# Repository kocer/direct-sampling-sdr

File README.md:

# Direct-Sampling SDR

A direct-sampling software-defined radio transceiver and its power
amplifier for the amateur bands from 1.8 MHz to 54 MHz.

## What the equipment does

The receiver samples the antenna signal directly. It does not use a
mixer and it does not use an intermediate frequency. Four receive
channels operate at the same time. The four channels use one clock.
Thus the channels keep a constant phase relation.

The transmitter uses the same four channels in the opposite direction.
The power amplifier increases the transmit power to a maximum of 100 W.

| Item | Value |
|---|---|
| Frequency range | 1.8 MHz to 54 MHz |
| Receive channels | 4, phase coherent |
| Transmit channels | 4 |
| ADC | AD9251BCPZ-80, 14 bit, dual, 80 MSPS |
| DAC | AD9767, 14 bit, dual, operated at 80 MSPS |
| FPGA | Lattice ECP5 LFE5U-25F, BG256 |
| Filter bands | 7 for each channel |
| Amplifier power | 5, 10, 25, 50, 75 and 100 W |
| Amplifier class | A, at all power levels |
| Host interface | 2 x gigabit ethernet |
| Sample clock | 80.000 MHz VCXO, ABLNO-V |
| Clock jitter | 81 fs narrow band, 162 fs wide band |
| Reference | 10 MHz external, or GPS |

## The three boards

| Board | Function | Size | Layers |
|---|---|---|---|
| A | Main board: ADC, DAC, FPGA, ethernet | 235 x 225 mm | 6 |
| C | RF board: filters, transmit/receive relays | 350 x 235 mm | 2 |
| D | Power amplifier: driver, finals, low-pass filters | 275 x 185 mm | 2 |

Board B does not exist. The first design had a separate clock board.
The clock circuit is now on board A, because the distance from the clock
to the ADC controls the phase accuracy.

## Signal path

The receive path:

1. The antenna connects to board C.
2. The band filter removes the unwanted signals.
3. The transmit/receive relay connects the filter to the receive path.
4. The attenuator sets the signal level.
5. Board A receives the signal.
6. The transformer makes the signal differential.
7. The ADC samples the signal.
8. The FPGA processes the samples.
9. The ethernet interface sends the data to the host.

The transmit path:

1. The host sends the data to board A.
2. The DAC makes the analog signal.
3. Board D receives the signal.
4. The driver stage increases the power.
5. The four final transistors increase the power to 100 W.
6. The low-pass filter removes the harmonics.
7. The directional coupler measures the forward and the reflected power.
8. The antenna radiates the signal.

## Why direct sampling

A superheterodyne receiver mixes the input signal to a lower frequency.
The mixer makes unwanted products. The local oscillator adds noise.
Each conversion stage adds distortion.

A direct-sampling receiver has none of these stages. The ADC samples the
antenna signal. The remaining signal path is digital, thus it is exact
and it does not change with the temperature.

The clock sets the limit at high frequency. The jitter of the clock
gives this maximum signal-to-noise ratio:

    SNR = -20 x log10(2 x pi x f x t_jitter)

The VCXO contributes 60 fs and the fan-out buffer adds 54 fs in a narrow
band or 150 fs in a wide band. Together they give 81 fs and 162 fs.

| Input frequency | Jitter | SNR limit | What limits the result |
|---|---|---|---|
| 30 MHz | 81 fs | 96 dB | The noise of the ADC |
| 500 MHz | 81 fs | 72 dB | At the limit |
| 500 MHz | 162 fs | 66 dB | The jitter of the clock |

In the amateur bands the noise of the ADC is the limit and the clock is
not. The clock becomes the limit only when the receiver undersamples
near 500 MHz. A better clock part costs ten times more, and 66 dB is
still 11 effective bits.

## Why four coherent channels

Four channels that share one clock keep a constant phase relation. This
makes these functions possible:

- Removal of a local noise source with a second antenna
- Measurement of the direction of a signal
- Increase of the antenna gain in one direction
- Measurement of meteor trails with two or more sites

A receiver with one channel cannot do these functions.

## Licenses

| Content | License |
|---|---|
| Hardware design | CERN-OHL-S-2.0 |
| Software and scripts | GPL-3.0 |
| Documentation | CC-BY-SA-4.0 |

## Repository content

| Directory | Content |
|---|---|
| `hardware/kicad/A_main` | Board A: schematic, PCB, generator scripts |
| `hardware/kicad/C_rf` | Board C |
| `hardware/kicad/D_pa` | Board D |
| `hardware/kicad/lib` | Symbols and footprints |
| `gateware/rtl` | Verilog source for the ECP5 |
| `gateware/sim` | Test benches |
| `gateware/sentez` | Synthesis and place-and-route scripts |
| `docs` | Design documentation |

The schematics are not drawn by hand. Python scripts make them. Each
script writes one sheet. To change a sheet, change the script and run
it again. The document `docs/TOOLS.md` gives the procedure.

## Status

The three schematics are complete. The electrical rule check finds no
errors on the three boards. The placement is complete. The routing is
in progress. No board is ready for manufacture.

The gateware operates in simulation. 21 test benches pass. The design
fits in the ECP5-25F and it meets the timing of all five clocks. The
receive chain, the transmit chain, the packet interface and the
control interface are complete. The SDRAM interface and the digital
predistortion do not exist.

Verification tools examine the boards and the schematics. They find
faults that the electrical rule check cannot find. An example: a
symbol pin number that does not agree with a footprint pad number
makes a net that goes nowhere, but the rule check sees a correct
wire. The commit messages give the details of each fault.

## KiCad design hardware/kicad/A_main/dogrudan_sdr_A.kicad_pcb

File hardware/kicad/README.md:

# KiCad çalışma dizini

```
lib/dogrudan-sdr.kicad_sym   sembol kütüphanesi
lib/gen_symbols.py           üreteç — sembolleri BU yazıyor, elle düzenleme
lib/ATTRIBUTION.md           ECP5 sembolü kaynağı ve lisansı
A_main/                      A kartı (ADC+DAC+saat+FPGA+PHY+güç)
C_frontend/                  C kartı (koruma+T/R+zayıflatıcı+ön seçici)
```

## Semboller

| Sembol | Pin | Birim | Kaynak | Durum |
|---|---|---|---|---|
| ECP5-BGA256 | 256 | 8 | Cynthion (CERN-OHL-P) | pin uyumu doğrulandı |
| AD9251 | 65 | 4 | datasheet Rev.C s.11-12 | görsel doğrulandı |
| AD9767 | 48 | 3 | datasheet Rev.G s.9-10 | pin sayımı doğrulandı |
| RTL8211F | 41 | 2 | datasheet Rev.1.1 s.14-17 | görsel doğrulandı |
| PE4312 | 21 | 1 | DOC-81482-4.01 s.15 | pin sayımı doğrulandı |
| ADP150 | 5 | 1 | datasheet Rev.E s.6 | — |
| ABLNO-V | 4 | 1 | Abracon ABLNO s.8 | **doğrulandı** |

KiCad standart kütüphanesinden ayrıca: `W25Q128JVS`, `TPS62130`, `TPS7A20`.

## Üreteci kullan, dosyayı elle düzenleme

```bash
cd lib
python3 gen_symbols.py          # kütüphaneye ekler
kicad-cli sym export svg -o /tmp/s dogrudan-sdr.kicad_sym
rsvg-convert -w 800 /tmp/s/AD9251_unit1.svg -o /tmp/x.png   # gözle bak
```

`gen_symbols.py` kutu geometrisini pin sayısı **ve isim uzunluklarından**
hesaplıyor. Elle kutu yazma; iki kere denedim, ikisinde de pin gövdesi
kutunun içinde kaldı ve o pine tel bağlanamadı.

> Üreteç kütüphaneye **ekliyor**, sıfırlamıyor. Yeniden üretmeden önce
> temiz kütüphaneyi geri yükle, yoksa semboller tekrarlanır.

## Doğrulanmış footprint'ler

Hepsi KiCad 10 standart kütüphanesinde:

```
BGA-256_14.0x14.0mm_Layout16x16_P0.8mm      ECP5 caBGA-256
QFN-64-1EP_9x9mm_P0.5mm_EP3.8x3.8mm         AD9251 LFCSP-64
LQFP-48_7x7mm_P0.5mm                        AD9767
QFN-40-1EP_5x5mm_P0.4mm_EP3.8x3.8mm         RTL8211F
QFN-20-1EP_4x4mm_P0.5mm_EP2.6x2.6mm         PE4312
TSOT-23-5                                   ADP150
```

ABLNO ayak izi bu depoda çizildi: `lib/dogrudan-sdr.pretty/`
`Oscillator_Abracon_ABLNO_4pad_14.3x8.7mm.kicad_mod`
Gövde 14.30 × 8.70 mm, 4 ped 2.5 × 1.5 mm, aralık 5.08 × 5.80 mm.

> Pin-1 işaretini ilk çizişte yanlış köşeye koydum (pad 4'ün yanına).
> Parçanın 180° ters lehimlenmesine yol açardı. SVG'ye bakınca yakalandı.
> **Her ayak izini çizdikten sonra render edip gözle bak.**

## Sıradaki adım: netlist şartnamesi

Şema üretmeden önce **hangi pin nereye** yazılacak, insan okuyabilir metin
olarak. Sebep: 256 pinlik BGA'nın bağlantılarını doğrudan `.kicad_sch`
dosyasına yazmak görsel olarak doğrulanamaz. Şartname gözden geçirilebilir,
şema ondan üretilir.

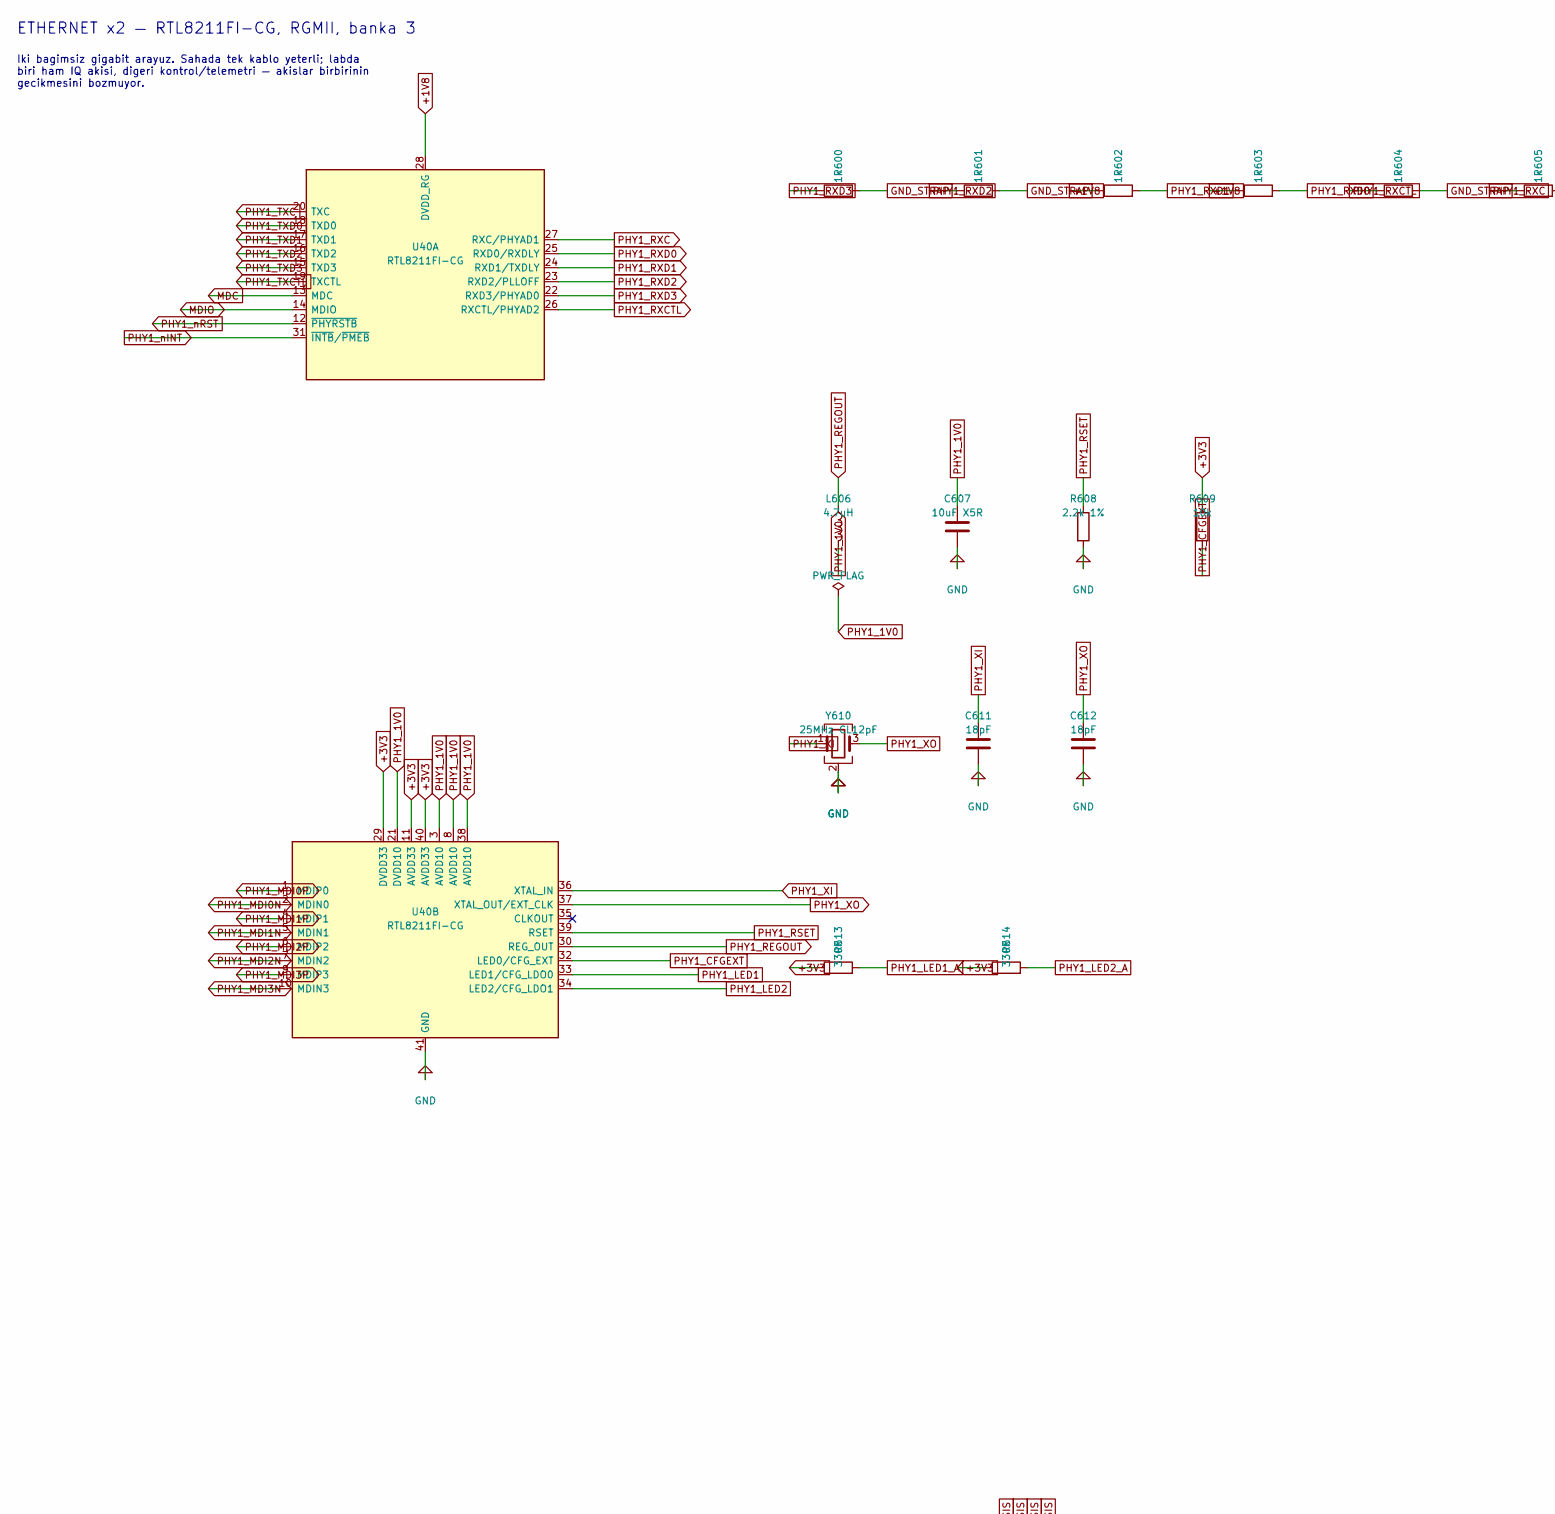
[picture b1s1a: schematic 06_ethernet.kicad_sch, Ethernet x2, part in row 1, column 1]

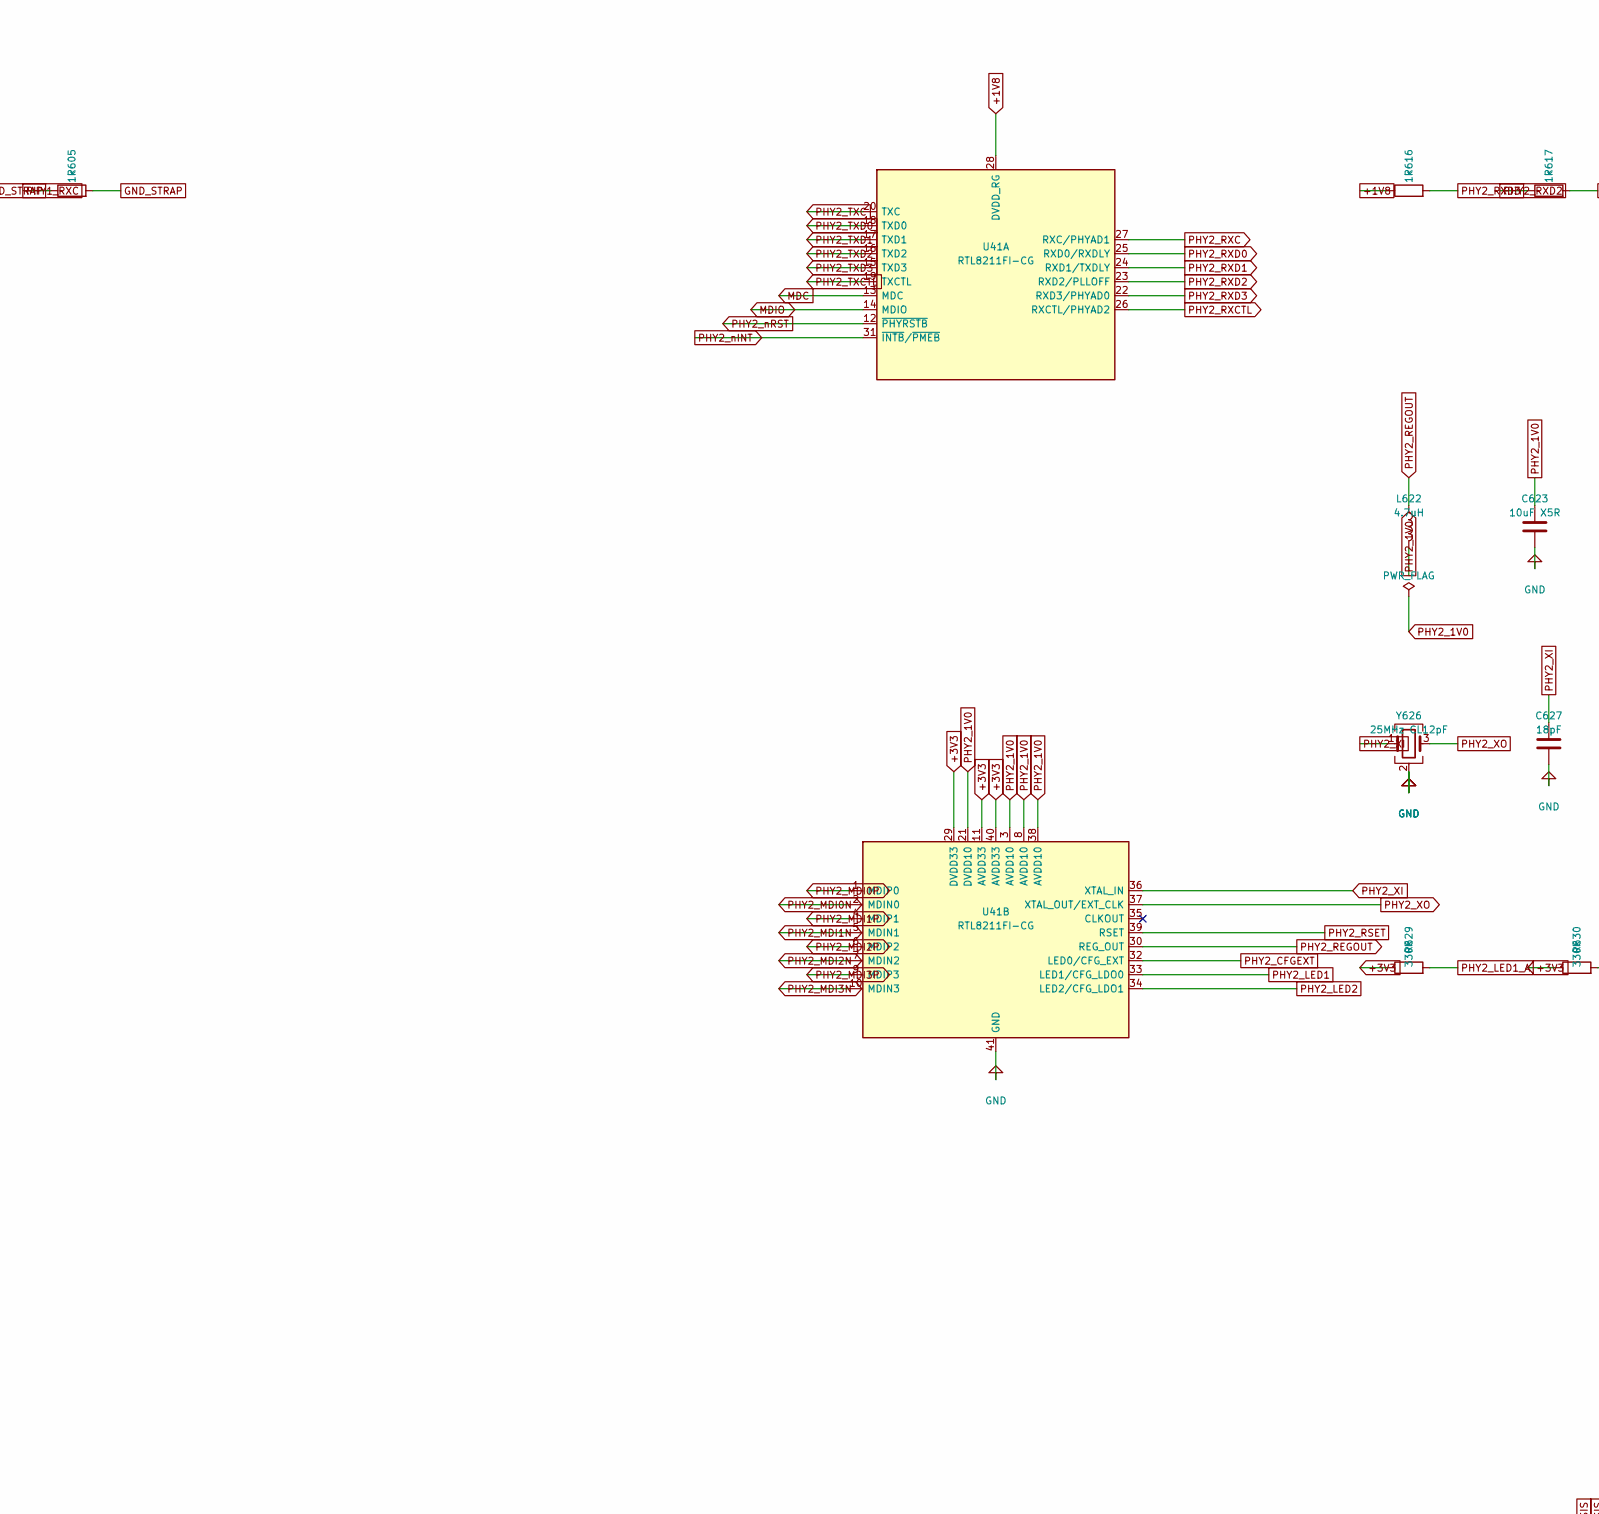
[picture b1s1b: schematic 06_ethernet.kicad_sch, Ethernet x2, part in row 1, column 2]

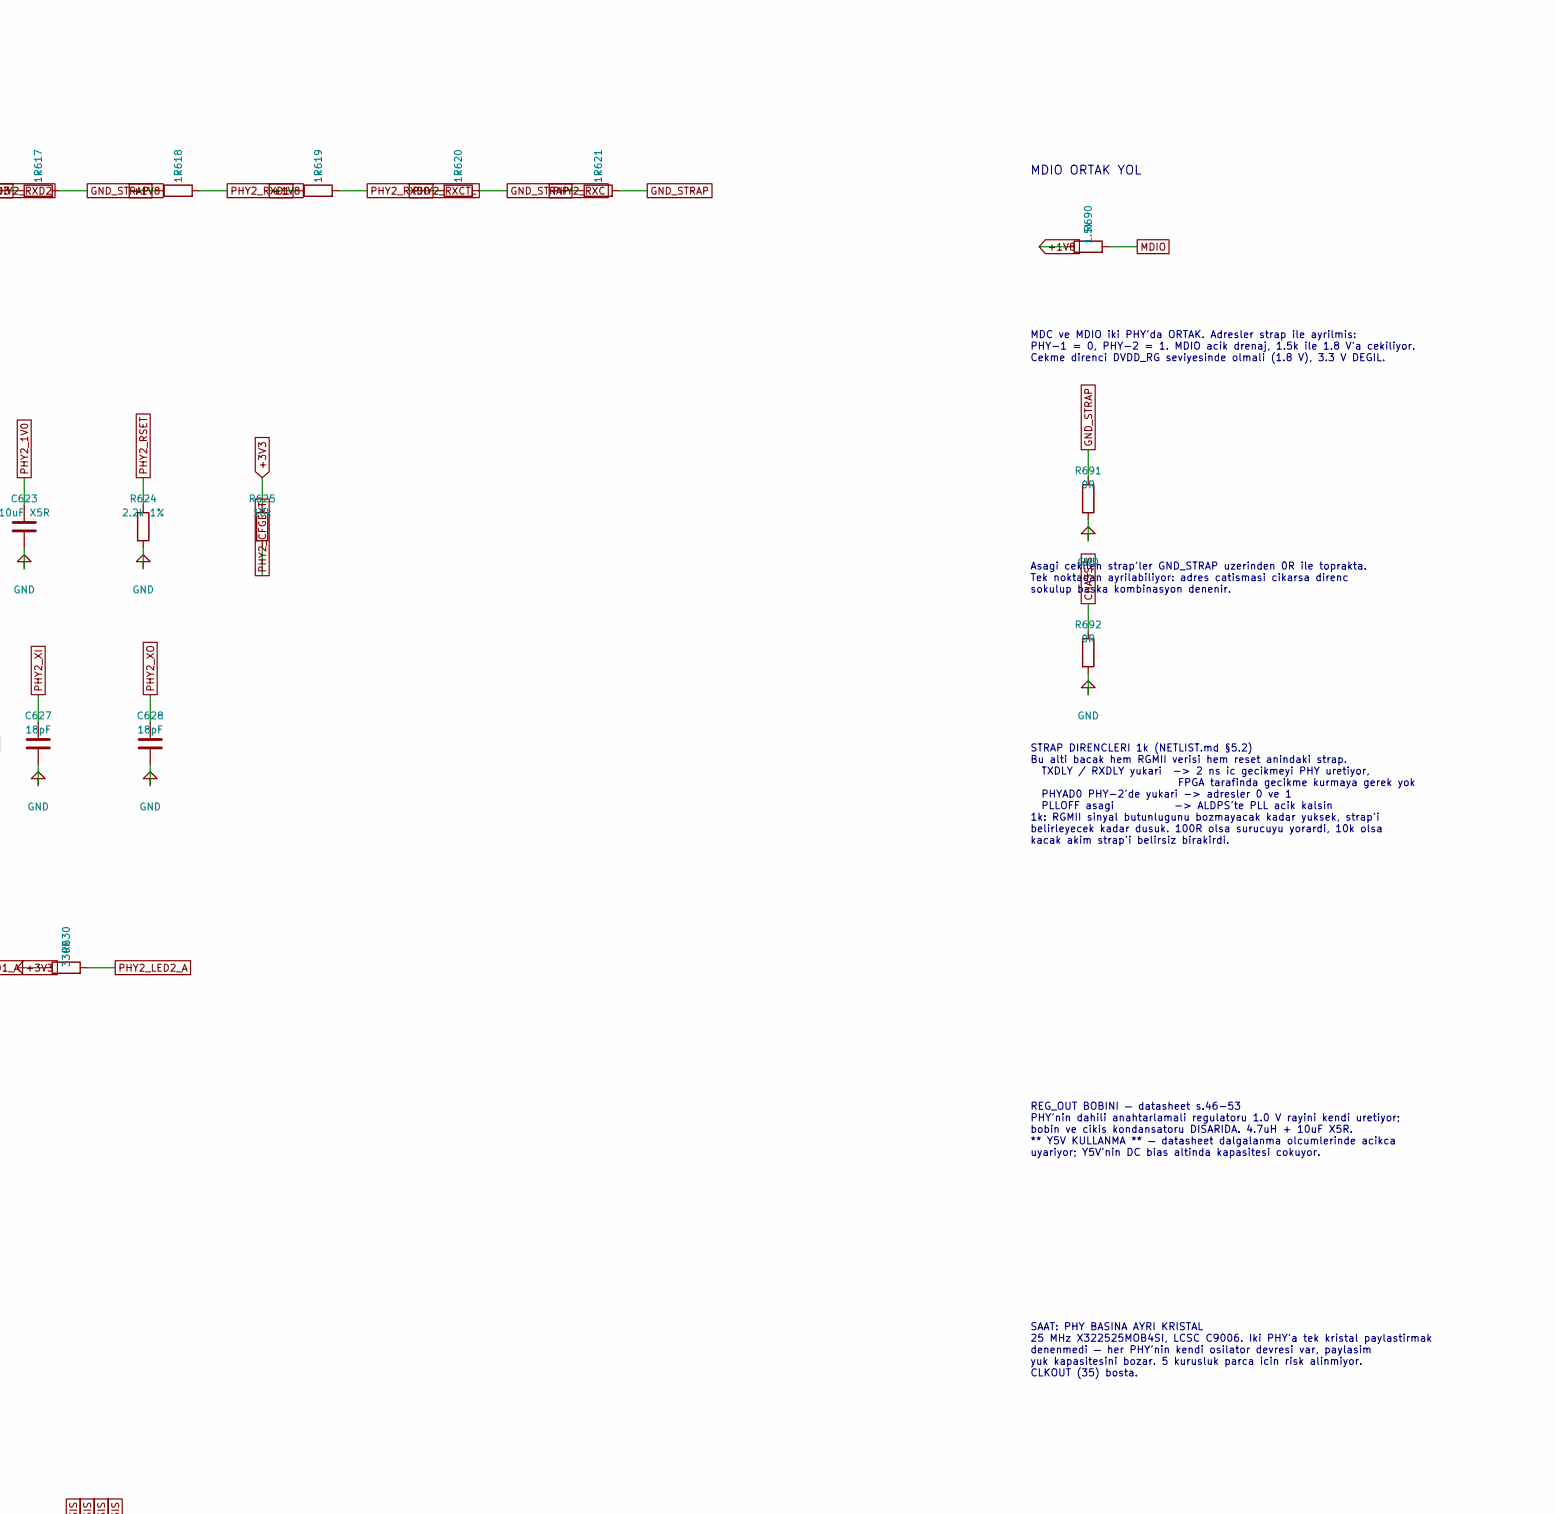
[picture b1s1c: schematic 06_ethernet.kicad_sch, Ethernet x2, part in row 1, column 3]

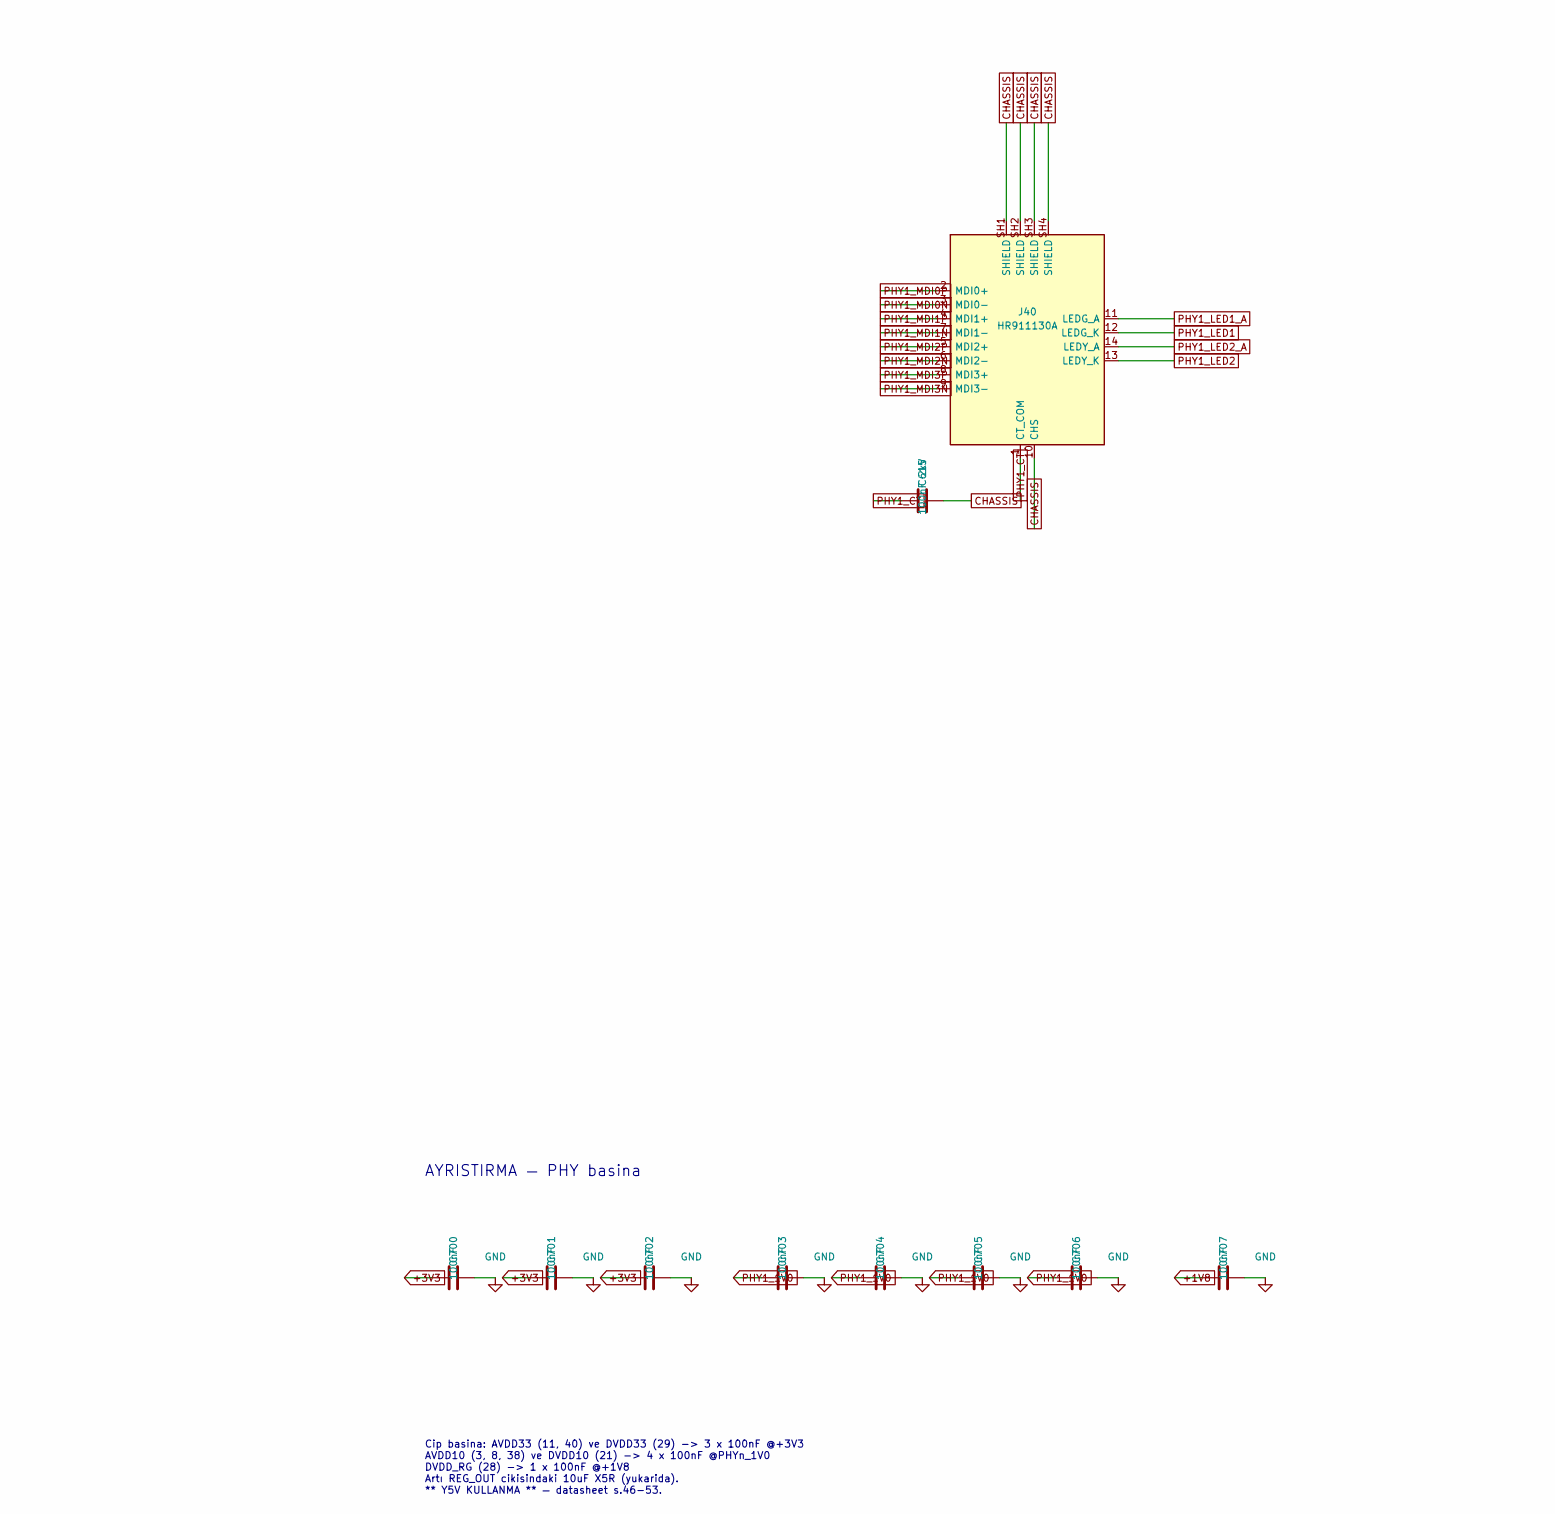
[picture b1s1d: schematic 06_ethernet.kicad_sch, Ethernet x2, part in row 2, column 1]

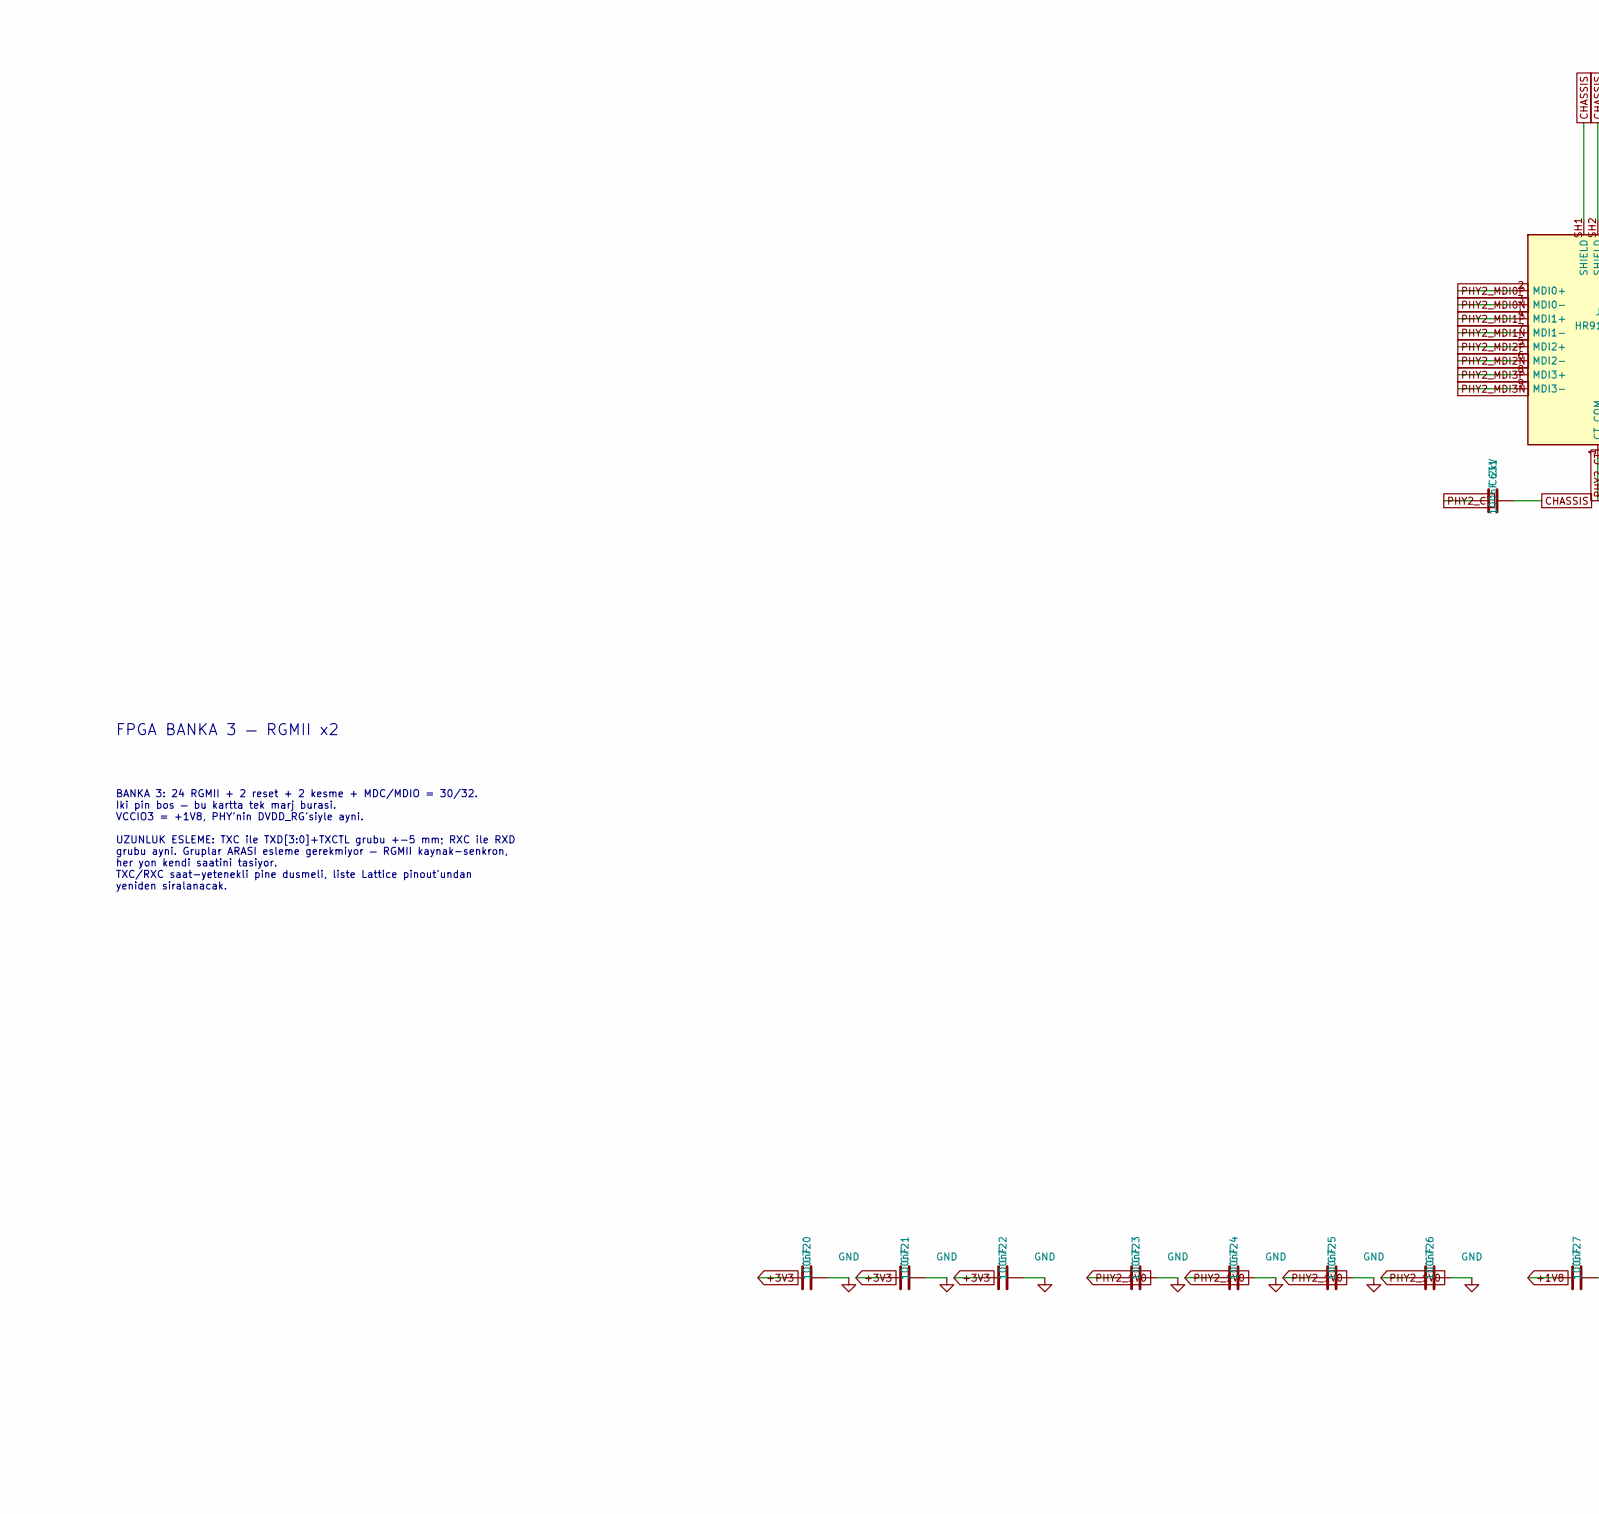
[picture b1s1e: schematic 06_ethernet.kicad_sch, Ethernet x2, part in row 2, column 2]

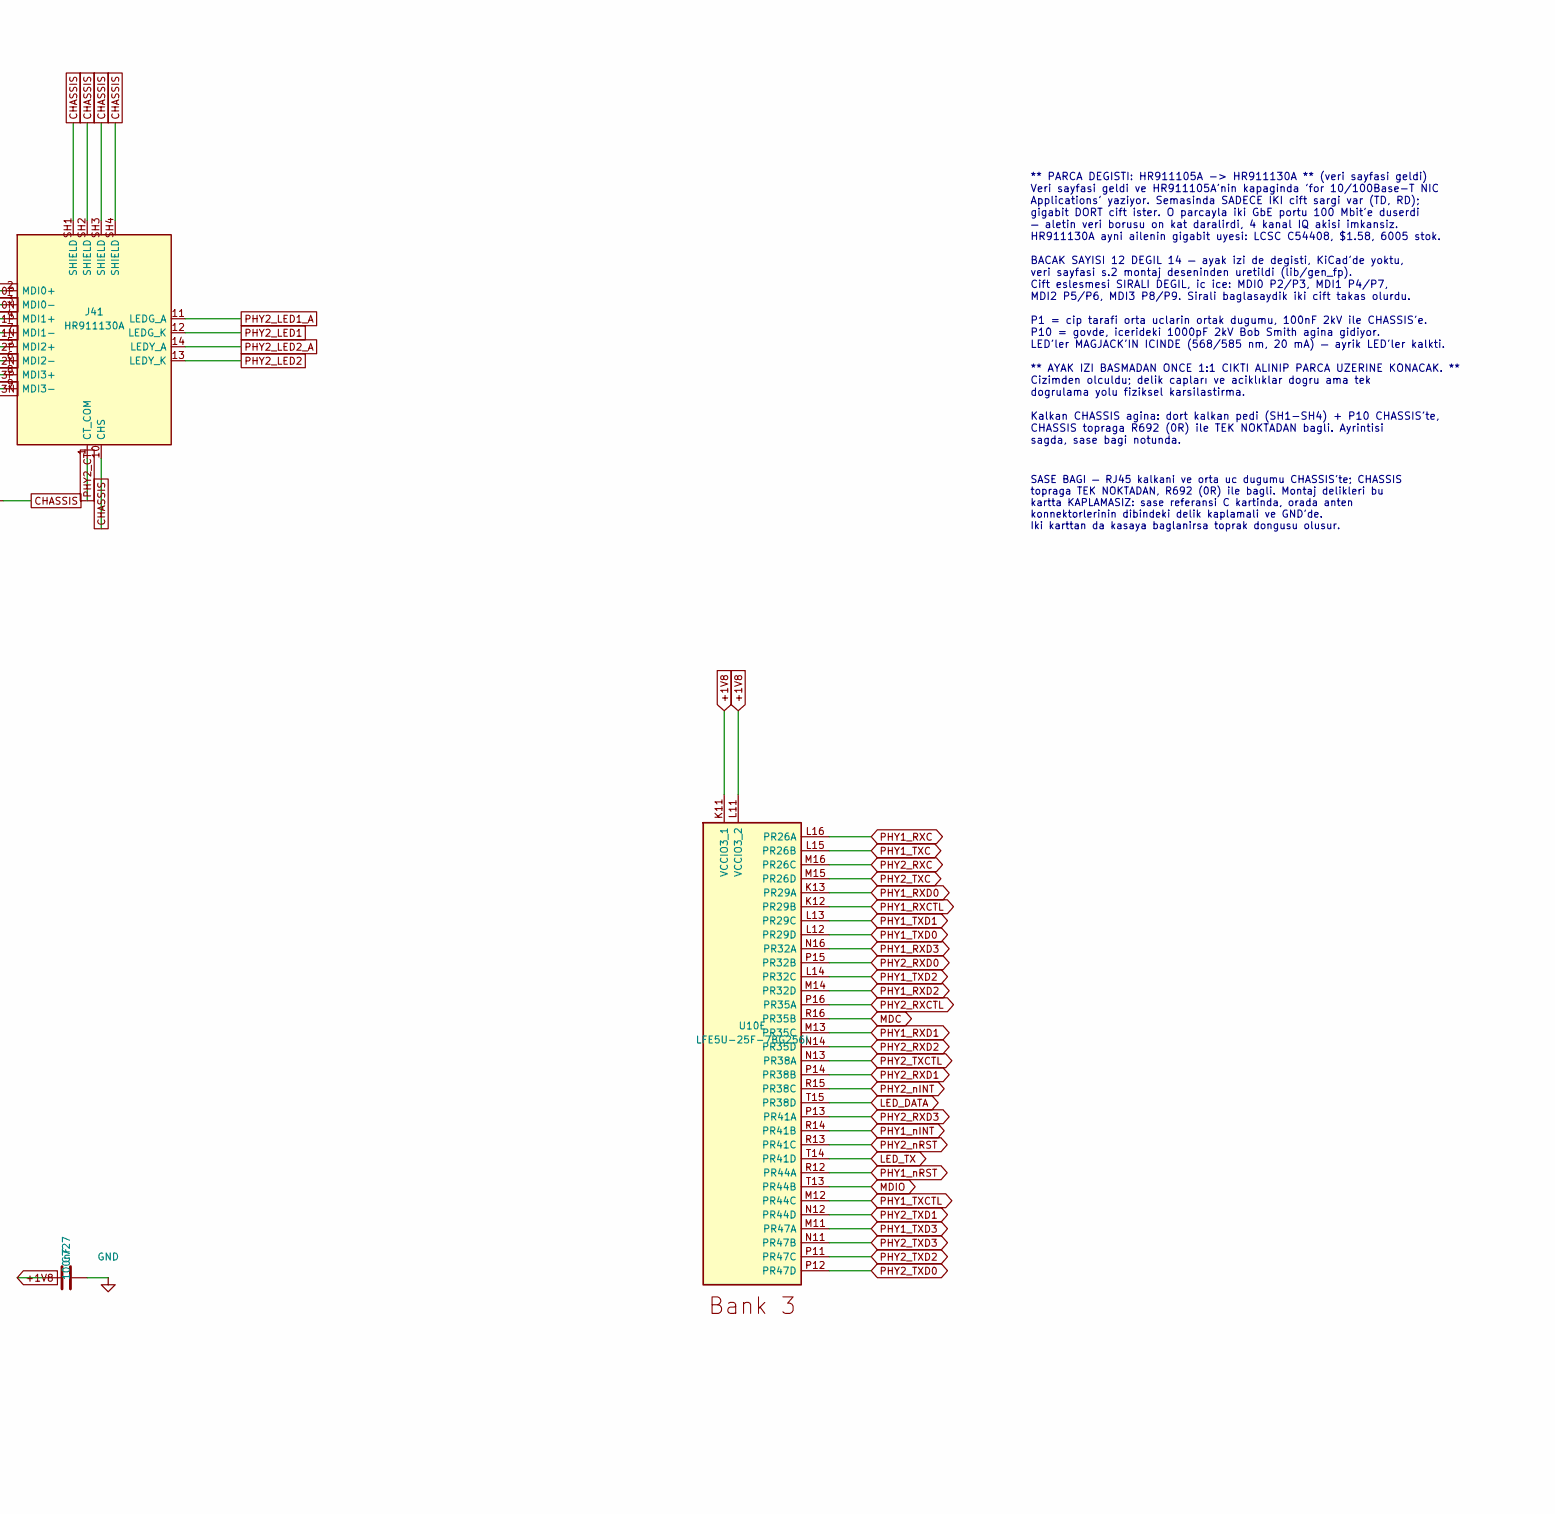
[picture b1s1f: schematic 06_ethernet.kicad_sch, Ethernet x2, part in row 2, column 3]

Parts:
C607, C623: 10uF X5R; C_0603_1608Metric
C611, C612, C627, C628: 18pF; C_0603_1608Metric
C615, C631: 100nF 2kV; C_0603_1608Metric
C700, C701, C702, C703, C704, C705, C706, C707, C720, C721, C722, C723, C724, C725, C726, C727: 100nF; C_0402_1005Metric
J40, J41: HR911130A; RJ45_Hanrun_HR911130A
L606, L622: 4.7uH; L_0805_2012Metric
R600, R601, R602, R603, R604, R605, R616, R617, R618, R619, R620, R621: 1k; R_0603_1608Metric
R608, R624: 2.2k 1%; R_0603_1608Metric
R609, R625: 10k; R_0603_1608Metric
R613, R614, R629, R630: 330R; R_0603_1608Metric
R690: 1.5k; R_0603_1608Metric
R691, R692: 0R; R_0603_1608Metric
U10: LFE5U-25F-7BG256I; BGA-256_14.0x14.0mm_Layout16x16_P0.8mm_Ball0.45mm_Pad0.32mm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
U40, U41: RTL8211FI-CG; QFN-40-1EP_5x5mm_P0.4mm_EP3.6x3.6mm
Y610, Y626: 25MHz CL12pF; Crystal_SMD_3225-4Pin_3.2x2.5mm

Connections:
+1V8: C707.1, C727.1, R602.1, R603.1, R616.1, R618.1, R619.1, R690.1, U10.K11 (VCCIO3_1), U10.L11 (VCCIO3_2), U40.28 (DVDD_RG), U41.28 (DVDD_RG); also elsewhere on the board
CHASSIS: C615.2, C631.2, J40.10 (CHS), J40.SH1 (SHIELD), J40.SH2 (SHIELD), J40.SH3 (SHIELD), J40.SH4 (SHIELD), J41.10 (CHS), J41.SH1 (SHIELD), J41.SH2 (SHIELD), J41.SH3 (SHIELD), J41.SH4 (SHIELD), R692.1
GND_STRAP: R600.2, R601.2, R604.2, R605.2, R617.2, R620.2, R621.2, R691.1
LED_DATA: U10.T15 (PR38D); also elsewhere on the board
LED_TX: U10.T14 (PR41D); also elsewhere on the board
MDC: U10.R16 (PR35B), U40.13 (MDC), U41.13 (MDC)
MDIO: R690.2, U10.T13 (PR44B), U40.14 (MDIO), U41.14 (MDIO)
PHY1_CFGEXT: R609.2, U40.32 (LED0/CFG_EXT)
PHY1_CT: C615.1, J40.1 (CT_COM)
PHY1_LED1: J40.12 (LEDG_K), U40.33 (LED1/CFG_LDO0)
PHY1_LED1_A: J40.11 (LEDG_A), R613.2
PHY1_LED2: J40.13 (LEDY_K), U40.34 (LED2/CFG_LDO1)
PHY1_LED2_A: J40.14 (LEDY_A), R614.2
PHY1_MDI0N: J40.3 (MDI0-), U40.2 (MDIN0)
PHY1_MDI0P: J40.2 (MDI0+), U40.1 (MDIP0)
PHY1_MDI1N: J40.7 (MDI1-), U40.5 (MDIN1)
PHY1_MDI1P: J40.4 (MDI1+), U40.4 (MDIP1)
PHY1_MDI2N: J40.6 (MDI2-), U40.7 (MDIN2)
PHY1_MDI2P: J40.5 (MDI2+), U40.6 (MDIP2)
PHY1_MDI3N: J40.9 (MDI3-), U40.10 (MDIN3)
PHY1_MDI3P: J40.8 (MDI3+), U40.9 (MDIP3)
PHY1_REGOUT: L606.1, U40.30 (REG_OUT)
PHY1_RSET: R608.1, U40.39 (RSET)
PHY1_RXC: R605.1, U10.L16 (PR26A), U40.27 (RXC/PHYAD1)
PHY1_RXCTL: R604.1, U10.K12 (PR29B), U40.26 (RXCTL/PHYAD2)
PHY1_RXD0: R603.2, U10.K13 (PR29A), U40.25 (RXD0/RXDLY)
PHY1_RXD1: R602.2, U10.M13 (PR35C), U40.24 (RXD1/TXDLY)
PHY1_RXD2: R601.1, U10.M14 (PR32D), U40.23 (RXD2/PLLOFF)
PHY1_RXD3: R600.1, U10.N16 (PR32A), U40.22 (RXD3/PHYAD0)
PHY1_TXC: U10.L15 (PR26B), U40.20 (TXC)
PHY1_TXCTL: U10.M12 (PR44C), U40.19 (TXCTL)
PHY1_TXD0: U10.L12 (PR29D), U40.18 (TXD0)
PHY1_TXD1: U10.L13 (PR29C), U40.17 (TXD1)
PHY1_TXD2: U10.L14 (PR32C), U40.16 (TXD2)
PHY1_TXD3: U10.M11 (PR47A), U40.15 (TXD3)
PHY1_XI: C611.1, U40.36 (XTAL_IN), Y610.1
PHY1_XO: C612.1, U40.37 (XTAL_OUT/EXT_CLK), Y610.3
PHY1_nINT: U10.R14 (PR41B), U40.31 (~INTB/~PMEB)
PHY1_nRST: U10.R12 (PR44A), U40.12 (~PHYRSTB)
PHY2_CFGEXT: R625.2, U41.32 (LED0/CFG_EXT)
PHY2_CT: C631.1, J41.1 (CT_COM)
PHY2_LED1: J41.12 (LEDG_K), U41.33 (LED1/CFG_LDO0)
PHY2_LED1_A: J41.11 (LEDG_A), R629.2
PHY2_LED2: J41.13 (LEDY_K), U41.34 (LED2/CFG_LDO1)
PHY2_LED2_A: J41.14 (LEDY_A), R630.2
PHY2_MDI0N: J41.3 (MDI0-), U41.2 (MDIN0)
PHY2_MDI0P: J41.2 (MDI0+), U41.1 (MDIP0)
PHY2_MDI1N: J41.7 (MDI1-), U41.5 (MDIN1)
PHY2_MDI1P: J41.4 (MDI1+), U41.4 (MDIP1)
PHY2_MDI2N: J41.6 (MDI2-), U41.7 (MDIN2)
PHY2_MDI2P: J41.5 (MDI2+), U41.6 (MDIP2)
PHY2_MDI3N: J41.9 (MDI3-), U41.10 (MDIN3)
PHY2_MDI3P: J41.8 (MDI3+), U41.9 (MDIP3)
PHY2_REGOUT: L622.1, U41.30 (REG_OUT)
PHY2_RSET: R624.1, U41.39 (RSET)
PHY2_RXC: R621.1, U10.M16 (PR26C), U41.27 (RXC/PHYAD1)
PHY2_RXCTL: R620.1, U10.P16 (PR35A), U41.26 (RXCTL/PHYAD2)
PHY2_RXD0: R619.2, U10.P15 (PR32B), U41.25 (RXD0/RXDLY)
PHY2_RXD1: R618.2, U10.P14 (PR38B), U41.24 (RXD1/TXDLY)
PHY2_RXD2: R617.1, U10.N14 (PR35D), U41.23 (RXD2/PLLOFF)
PHY2_RXD3: R616.2, U10.P13 (PR41A), U41.22 (RXD3/PHYAD0)
PHY2_TXC: U10.M15 (PR26D), U41.20 (TXC)
PHY2_TXCTL: U10.N13 (PR38A), U41.19 (TXCTL)
PHY2_TXD0: U10.P12 (PR47D), U41.18 (TXD0)
PHY2_TXD1: U10.N12 (PR44D), U41.17 (TXD1)
PHY2_TXD2: U10.P11 (PR47C), U41.16 (TXD2)
PHY2_TXD3: U10.N11 (PR47B), U41.15 (TXD3)
PHY2_XI: C627.1, U41.36 (XTAL_IN), Y626.1
PHY2_XO: C628.1, U41.37 (XTAL_OUT/EXT_CLK), Y626.3
PHY2_nINT: U10.R15 (PR38C), U41.31 (~INTB/~PMEB)
PHY2_nRST: U10.R13 (PR41C), U41.12 (~PHYRSTB)

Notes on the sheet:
REG_OUT BOBINI — datasheet s.46-53 PHY'nin dahili anahtarlamali regulatoru 1.0 V rayini kendi uretiyor; bobin ve cikis kondansatoru DISARIDA. 4.7uH + 10uF X5R. ** Y5V KULLANMA ** — datasheet dalgalanma olcumlerinde acikca uyariyor; Y5V'nin DC bias altinda kapasitesi cokuyor.
MDIO ORTAK YOL
FPGA BANKA 3 — RGMII x2
SAAT: PHY BASINA AYRI KRISTAL 25 MHz X322525MOB4SI, LCSC C9006. Iki PHY'a tek kristal paylastirmak denenmedi — her PHY'nin kendi osilator devresi var, paylasim yuk kapasitesini bozar. 5 kurusluk parca icin risk alinmiyor. CLKOUT (35) bosta.
MDC ve MDIO iki PHY'da ORTAK. Adresler strap ile ayrilmis: PHY-1 = 0, PHY-2 = 1. MDIO acik drenaj, 1.5k ile 1.8 V'a cekiliyor. Cekme direnci DVDD_RG seviyesinde olmali (1.8 V), 3.3 V DEGIL.
STRAP DIRENCLERI 1k (NETLIST.md §5.2) Bu alti bacak hem RGMII verisi hem reset anindaki strap. TXDLY / RXDLY yukari -> 2 ns ic gecikmeyi PHY uretiyor, FPGA tarafinda gecikme kurmaya gerek yok PHYAD0 PHY-2'de yukari -> adresler 0 ve 1 PLLOFF asagi -> ALDPS'te PLL acik kalsin 1k: RGMII sinyal butunlu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
ETHERNET x2 — RTL8211FI-CG, RGMII, banka 3
Cip basina: AVDD33 (11, 40) ve DVDD33 (29) -> 3 x 100nF @+3V3 AVDD10 (3, 8, 38) ve DVDD10 (21) -> 4 x 100nF @PHYn_1V0 DVDD_RG (28) -> 1 x 100nF @+1V8 Artı REG_OUT cikisindaki 10uF X5R (yukarida). ** Y5V KULLANMA ** — datasheet s.46-53.
SASE BAGI — RJ45 kalkani ve orta uc dugumu CHASSIS'te; CHASSIS topraga TEK NOKTADAN, R692 (0R) ile bagli. Montaj delikleri bu kartta KAPLAMASIZ: sase referansi C kartinda, orada anten konnektorlerinin dibindeki delik kaplamali ve GND'de. Iki karttan da kasaya baglanirsa toprak dongusu olusur.
** PARCA DEGISTI: HR911105A -> HR911130A ** (veri sayfasi geldi) Veri sayfasi geldi ve HR911105A'nin kapaginda 'for 10/100Base-T NIC Applications' yaziyor. Semasinda SADECE IKI cift sargi var (TD, RD); gigabit DORT cift ister. O parcayla iki GbE portu 100 Mbit'e duserdi — aletin veri borusu on kat 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
BANKA 3: 24 RGMII + 2 reset + 2 kesme + MDC/MDIO = 30/32. Iki pin bos — bu kartta tek marj burasi. VCCIO3 = +1V8, PHY'nin DVDD_RG'siyle ayni. UZUNLUK ESLEME: TXC ile TXD[3:0]+TXCTL grubu +-5 mm; RXC ile RXD grubu ayni. Gruplar ARASI esleme gerekmiyor — RGMII kaynak-senkron, her yon kendi saatini ta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
Asagi cekilen strap'ler GND_STRAP uzerinden 0R ile toprakta. Tek noktadan ayrilabiliyor: adres catismasi cikarsa direnc sokulup baska kombinasyon denenir.
AYRISTIRMA — PHY basina
Iki bagimsiz gigabit arayuz. Sahada tek kablo yeterli; labda biri ham IQ akisi, digeri kontrol/telemetri — akislar birbirinin gecikmesini bozmuyor.

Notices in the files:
hardware/kicad/A_main/gen_02_clock.py:
SPDX-FileCopyrightText: Copyright (c) 2026 TA4DTA
SPDX-License-Identifier: CERN-OHL-S-2.0
hardware/kicad/A_main/01_power.kicad_sch:
Copyright (c) 2026 TA4DTA - lisans CERN-OHL-S-2.0
Donanim CERN-OHL-S-2.0 | HDL ve yazilim GPL-3.0-only | belgeler CC-BY-SA-4.0
